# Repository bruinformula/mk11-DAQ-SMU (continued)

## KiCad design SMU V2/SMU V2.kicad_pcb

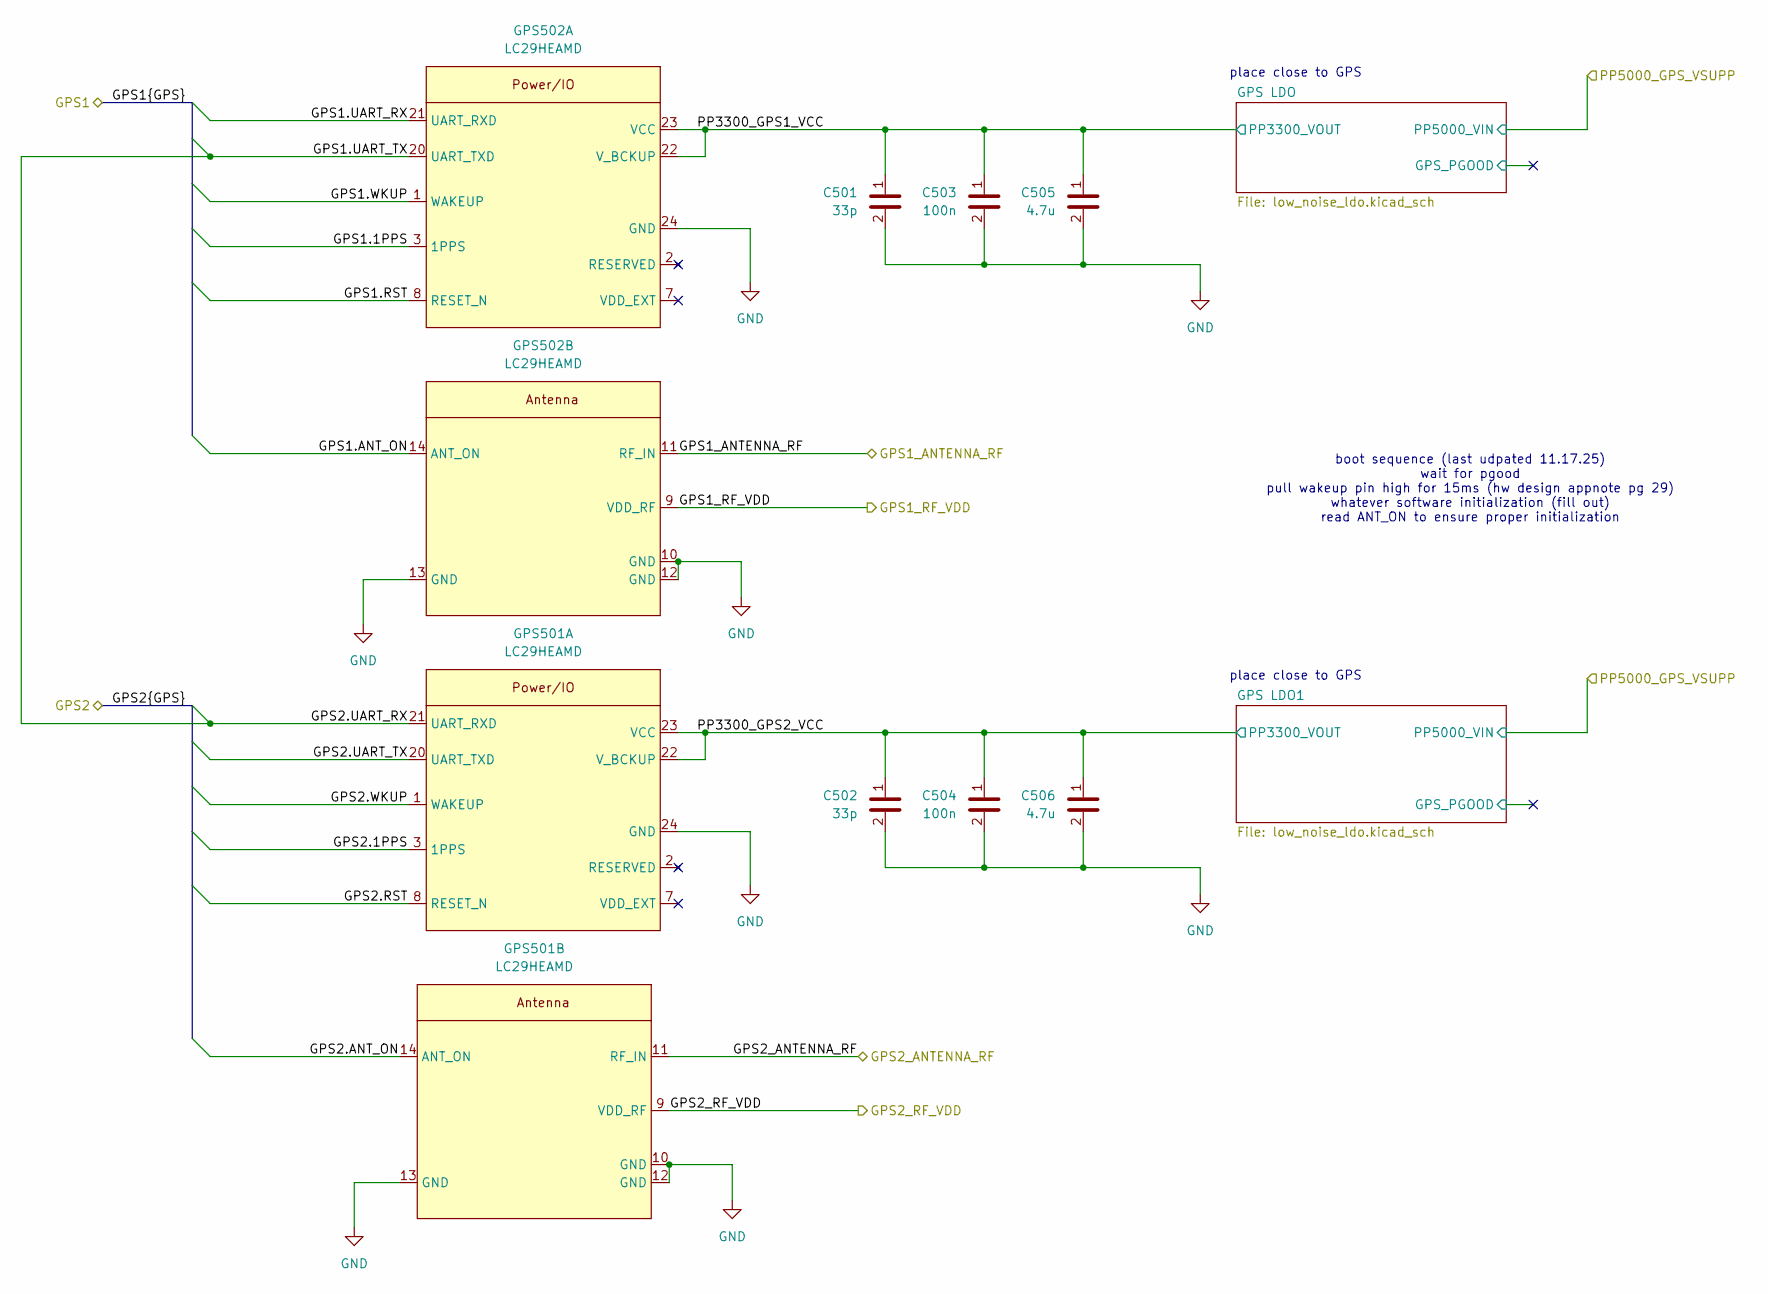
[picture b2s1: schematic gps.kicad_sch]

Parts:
C501, C502: 33p; C_0402_1005Metric_Pad0.74x0.62mm_HandSolder; LCSC P/N C1562
C503, C504: 100n; C_0402_1005Metric_Pad0.74x0.62mm_HandSolder; LCSC P/N C1525
C505, C506: 4.7u; C_0603_1608Metric_Pad1.08x0.95mm_HandSolder; LCSC P/N C19666
GPS501, GPS502: LC29HEAMD; Quectel LC49

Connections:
/Antenna1/GPS1_RF_VDD: GPS502.9 (VDD_RF); also elsewhere on the board
/Antenna2/GPS2_RF_VDD: GPS501.9 (VDD_RF); also elsewhere on the board
/GPS1.1PPS: GPS502.3 (1PPS); also elsewhere on the board
/GPS1.ANT_ON: GPS502.14 (ANT_ON); also elsewhere on the board
/GPS1.RST: GPS502.8 (RESET_N); also elsewhere on the board
/GPS1.UART_RX: GPS502.21 (UART_RXD); also elsewhere on the board
/GPS1.WKUP: GPS502.1 (WAKEUP); also elsewhere on the board
/GPS1_ANTENNA_RF: GPS502.11 (RF_IN); also elsewhere on the board
/GPS2.1PPS: GPS501.3 (1PPS); also elsewhere on the board
/GPS2.ANT_ON: GPS501.14 (ANT_ON); also elsewhere on the board
/GPS2.RST: GPS501.8 (RESET_N); also elsewhere on the board
/GPS2.UART_RX: GPS501.21 (UART_RXD), GPS502.20 (UART_TXD); also elsewhere on the board
/GPS2.UART_TX: GPS501.20 (UART_TXD); also elsewhere on the board
/GPS2.WKUP: GPS501.1 (WAKEUP); also elsewhere on the board
/GPS2_ANTENNA_RF: GPS501.11 (RF_IN); also elsewhere on the board
/GPS/PP3300_GPS1_VCC: C501.1, C503.1, C505.1, GPS502.22 (V_BCKUP), GPS502.23 (VCC); also elsewhere on the board
/GPS/PP3300_GPS2_VCC: C502.1, C504.1, C506.1, GPS501.22 (V_BCKUP), GPS501.23 (VCC); also elsewhere on the board
GND: C501.2, C502.2, C503.2, C504.2, C505.2, C506.2, GPS501.10 (GND), GPS501.12 (GND), GPS501.13 (GND), GPS501.24 (GND), GPS502.10 (GND), GPS502.12 (GND), GPS502.13 (GND), GPS502.24 (GND); also elsewhere on the board

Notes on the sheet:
boot sequence (last udpated 11.17.25) wait for pgood pull wakeup pin high for 15ms (hw design appnote pg 29) whatever software initialization (fill out) read ANT_ON to ensure proper initialization
place close to GPS

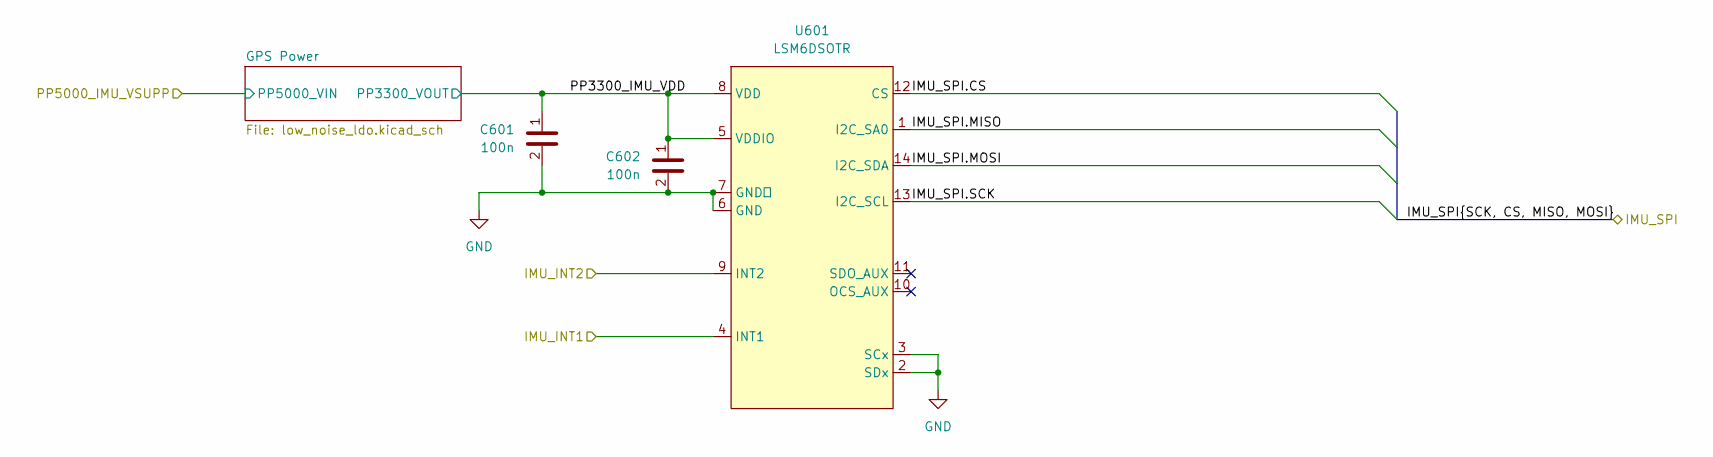
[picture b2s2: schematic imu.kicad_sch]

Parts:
C601, C602: 100n; C_0402_1005Metric_Pad0.74x0.62mm_HandSolder; LCSC P/N C1525
U601: LSM6DSOTR; LGA-14_3x2.5mm_P0.5mm_LayoutBorder3x4y; Manufacturer P/N LSM6DSOTR; Digikey P/N 497-18181-2-ND

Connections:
/IMU/IMU_INT1: U601.4 (INT1); also elsewhere on the board
/IMU/IMU_INT2: U601.9 (INT2); also elsewhere on the board
/IMU/PP3300_IMU_VDD: C601.1, C602.1, U601.5 (VDDIO), U601.8 (VDD); also elsewhere on the board
/IMU_SPI.CS: U601.12 (CS); also elsewhere on the board
/IMU_SPI.MISO: U601.1 (I2C_SA0); also elsewhere on the board
/IMU_SPI.MOSI: U601.14 (I2C_SDA); also elsewhere on the board
/IMU_SPI.SCK: U601.13 (I2C_SCL); also elsewhere on the board
GND: C601.2, C602.2, U601.2 (SDx), U601.3 (SCx), U601.6 (GND), U601.7 (GND); also elsewhere on the board

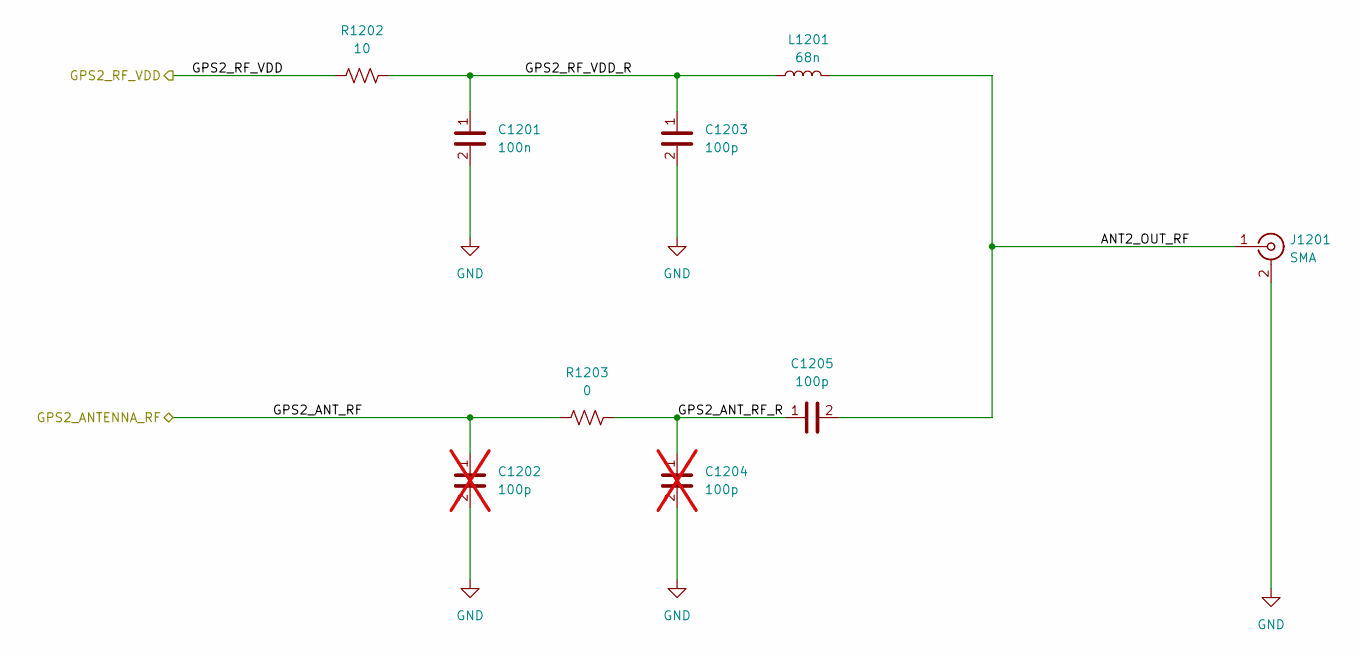
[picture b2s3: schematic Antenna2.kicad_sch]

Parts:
C1201: 100n; C_0402_1005Metric_Pad0.74x0.62mm_HandSolder; Manufacturer P/N CL05B104KB54PNC; LCSC P/N C307331
C1202, C1204: 100p; C_0402_1005Metric_Pad0.74x0.62mm_HandSolder; LCSC P/N C1546; not fitted
C1203, C1205: 100p; C_0402_1005Metric_Pad0.74x0.62mm_HandSolder; LCSC P/N C1546
J1201: SMA; THT SMA; Manufacturer P/N SMA-J-P-H-ST-TH1; Digikey P/N SAM8971-ND
L1201: 68n; L_0402_1005Metric_Pad0.77x0.64mm_HandSolder; Manufacturer P/N LQW15AN68NG0ZD; Digikey P/N 490-17700-2-ND
R1202: 10; R_0402_1005Metric_Pad0.72x0.64mm_HandSolder; Mouser P/N 708-RMCF0402FT10R0; Digikey P/N RMCF0402FT10R0CT-ND
R1203: 0; R_0402_1005Metric_Pad0.72x0.64mm_HandSolder; Mouser P/N 708-RMCF0402ZT0R00; Digikey P/N RMCF0402ZT0R00CT-ND

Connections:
/Antenna2/ANT2_OUT_RF: C1205.2, J1201.1, L1201.1
/Antenna2/GPS2_ANT_RF_R: C1204.1, C1205.1, R1203.2
/Antenna2/GPS2_RF_VDD: R1202.1; also elsewhere on the board
/Antenna2/GPS2_RF_VDD_R: C1201.1, C1203.1, L1201.2, R1202.2
/GPS2_ANTENNA_RF: C1202.1, R1203.1; also elsewhere on the board
GND: C1201.2, C1202.2, C1203.2, C1204.2, J1201.2; also elsewhere on the board

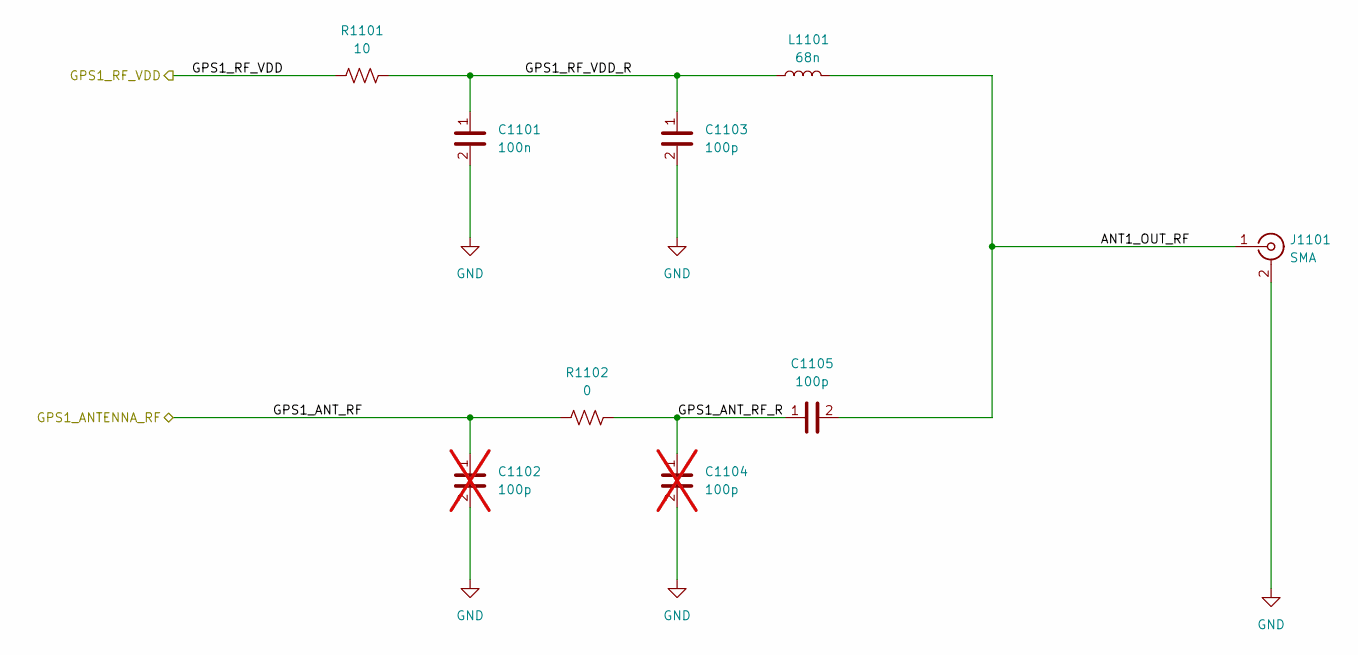
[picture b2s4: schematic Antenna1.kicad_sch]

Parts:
C1101: 100n; C_0402_1005Metric_Pad0.74x0.62mm_HandSolder; Manufacturer P/N CL05B104KB54PNC; LCSC P/N C307331
C1102, C1104: 100p; C_0402_1005Metric_Pad0.74x0.62mm_HandSolder; LCSC P/N C1546; not fitted
C1103, C1105: 100p; C_0402_1005Metric_Pad0.74x0.62mm_HandSolder; LCSC P/N C1546
J1101: SMA; THT SMA; Manufacturer P/N SMA-J-P-H-ST-TH1; Digikey P/N SAM8971-ND
L1101: 68n; L_0402_1005Metric_Pad0.77x0.64mm_HandSolder; Manufacturer P/N LQW15AN68NG0ZD; Digikey P/N 490-17700-2-ND
R1101: 10; R_0402_1005Metric_Pad0.72x0.64mm_HandSolder; Mouser P/N 708-RMCF0402FT10R0; Digikey P/N RMCF0402FT10R0CT-ND
R1102: 0; R_0402_1005Metric_Pad0.72x0.64mm_HandSolder; Mouser P/N 708-RMCF0402ZT0R00; Digikey P/N RMCF0402ZT0R00CT-ND

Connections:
/Antenna1/ANT1_OUT_RF: C1105.2, J1101.1, L1101.1
/Antenna1/GPS1_ANT_RF_R: C1104.1, C1105.1, R1102.2
/Antenna1/GPS1_RF_VDD: R1101.1; also elsewhere on the board
/Antenna1/GPS1_RF_VDD_R: C1101.1, C1103.1, L1101.2, R1101.2
/GPS1_ANTENNA_RF: C1102.1, R1102.1; also elsewhere on the board
GND: C1101.2, C1102.2, C1103.2, C1104.2, J1101.2; also elsewhere on the board

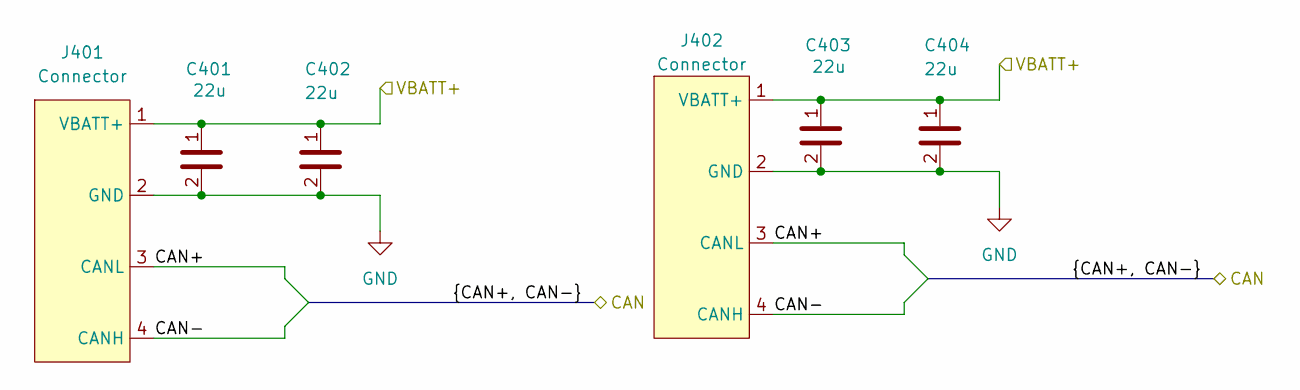
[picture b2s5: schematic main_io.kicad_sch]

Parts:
C401, C402, C403, C404: 22u; C_0805_2012Metric_Pad1.18x1.45mm_HandSolder; Mouser P/N 187-CL21A226MAYNNNE
J401, J402: Connector; Molex_Micro-Fit_3.0_43650-0400_1x04_P3.00mm_Horizontal; Manufacturer P/N 0436500401; Digikey P/N WM1867-ND

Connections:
/CAN+: J401.3 (CANL), J402.3 (CANL); also elsewhere on the board
/CAN-: J401.4 (CANH), J402.4 (CANH); also elsewhere on the board
/Main IO/VBATT+: C401.1, C402.1, C403.1, C404.1, J401.1 (VBATT+), J402.1 (VBATT+); also elsewhere on the board
GND: C401.2, C402.2, C403.2, C404.2, J401.2 (GND), J402.2 (GND); also elsewhere on the board

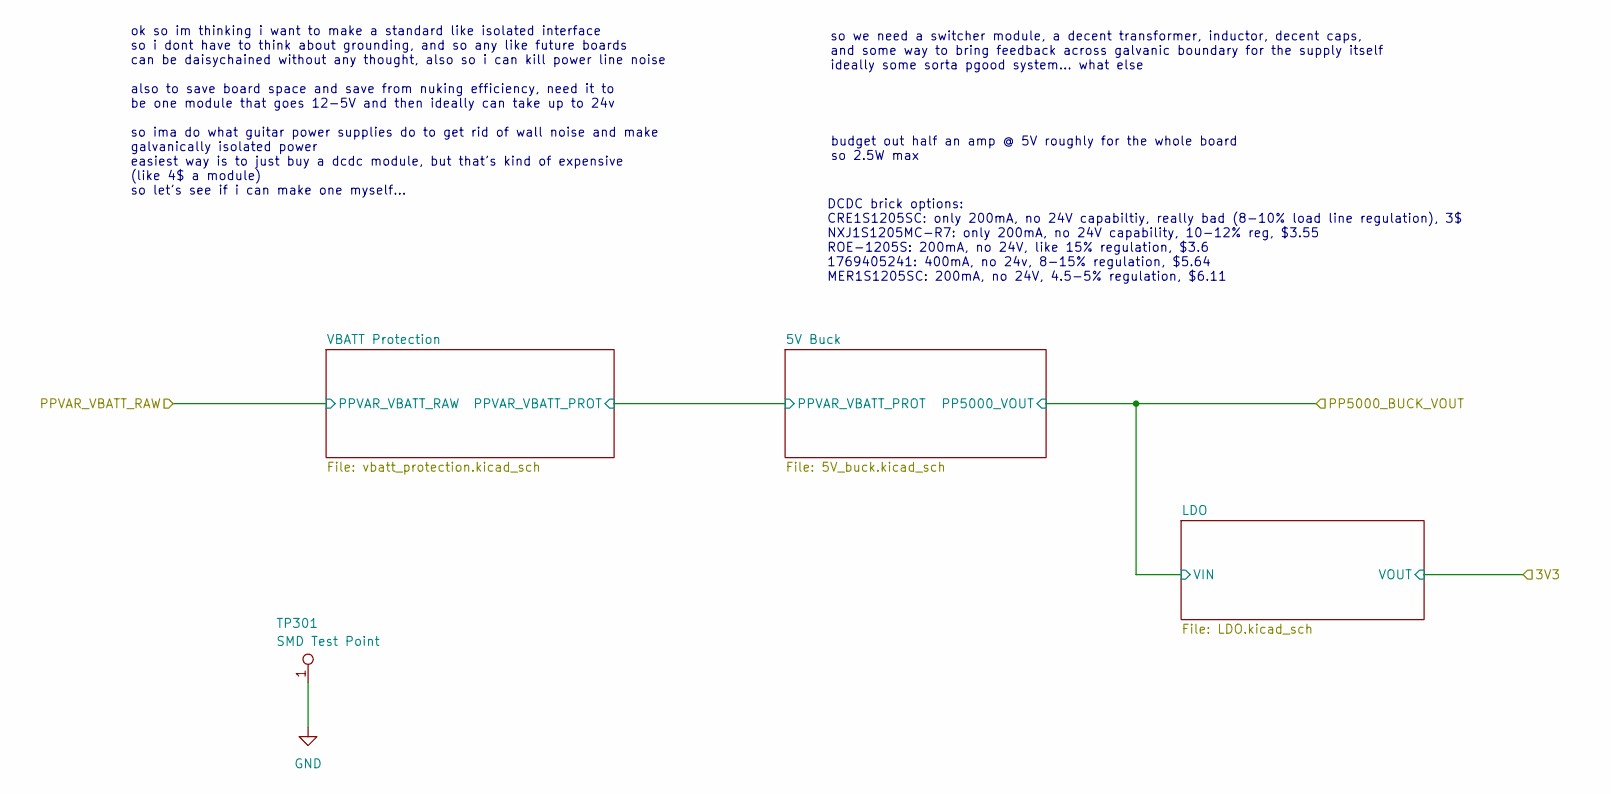
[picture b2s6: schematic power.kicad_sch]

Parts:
TP301: SMD Test Point; TestPoint_Keystone_5019_Miniature; Manufacturer P/N RH-5019; Digikey P/N 36-5019CT-ND

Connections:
GND: TP301.1; also elsewhere on the board

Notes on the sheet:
ok so im thinking i want to make a standard like isolated interface so i dont have to think about grounding, and so any like future boards can be daisychained without any thought, also so i can kill power line noise also to save board space and save from nuking efficiency, need it to be one module 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
so we need a switcher module, a decent transformer, inductor, decent caps, and some way to bring feedback across galvanic boundary for the supply itself ideally some sorta pgood system... what else
DCDC brick options: CRE1S1205SC: only 200mA, no 24V capabiltiy, really bad (8-10% load line regulation), 3$ NXJ1S1205MC-R7: only 200mA, no 24V capability, 10-12% reg, $3.55 ROE-1205S: 200mA, no 24V, like 15% regulation, $3.6 1769405241: 400mA, no 24v, 8-15% regulation, $5.64 MER1S1205SC: 200mA, no 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
budget out half an amp @ 5V roughly for the whole board so 2.5W max

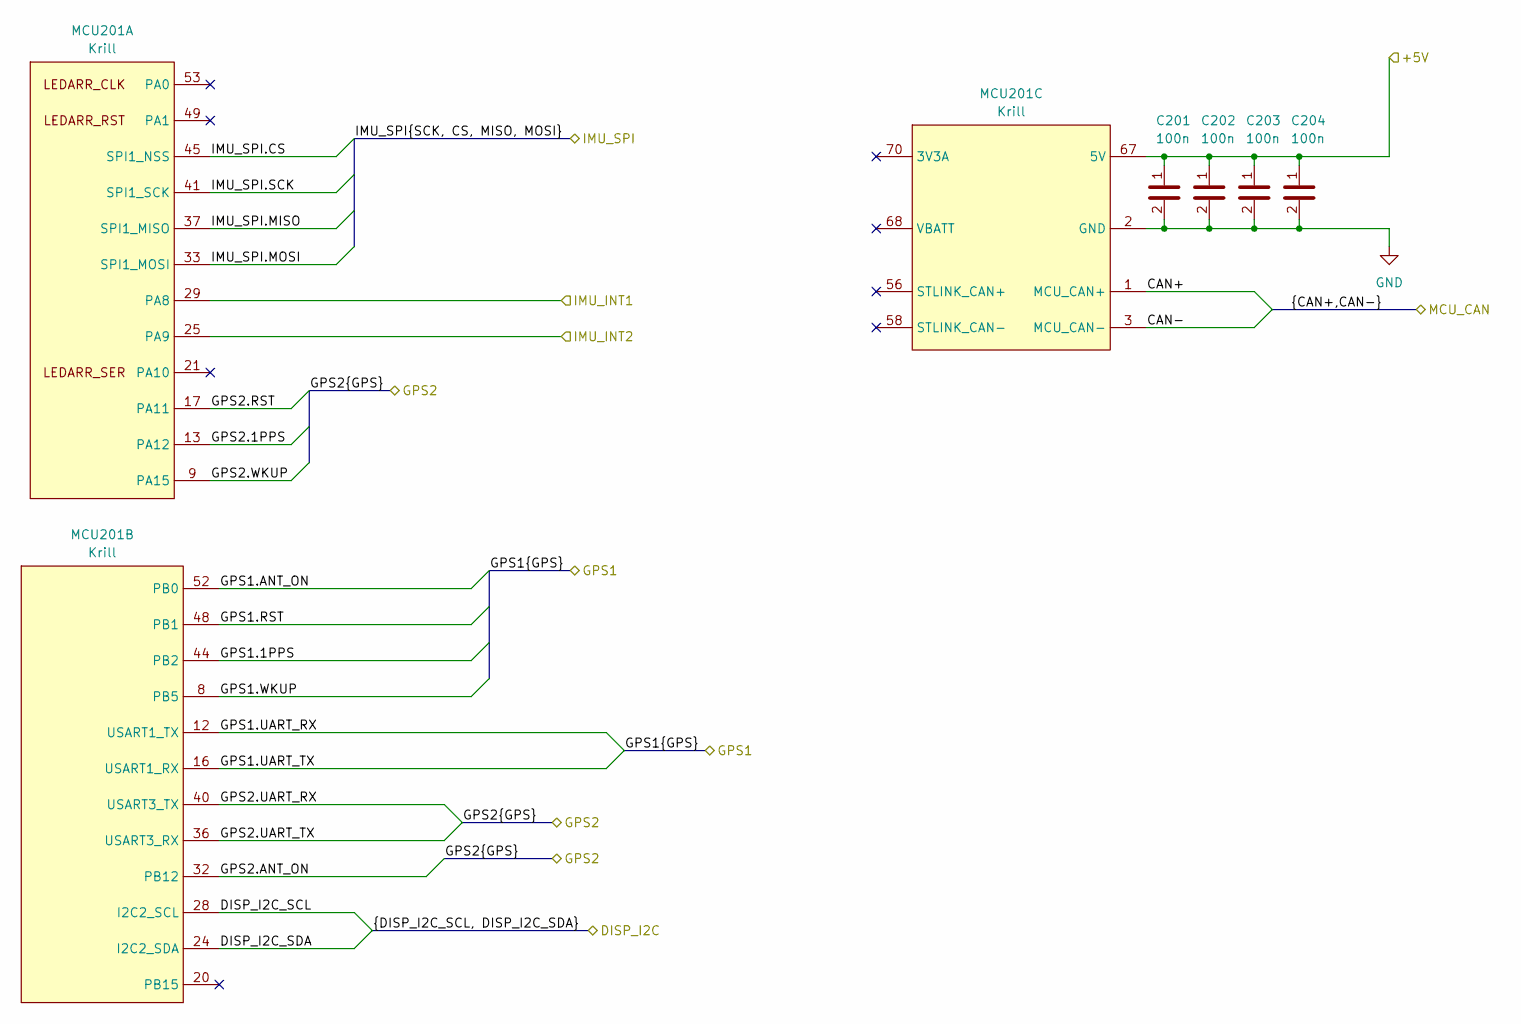
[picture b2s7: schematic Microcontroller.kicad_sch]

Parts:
C201, C202, C203, C204: 100n; C_0402_1005Metric_Pad0.74x0.62mm_HandSolder; LCSC P/N C1525
MCU201: Krill; Manufacturer P/N 2E0BC21-S85BM-7H; Digikey P/N 609-MDT850M01501CT-ND

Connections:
+5V: C201.1, C202.1, C203.1, C204.1, MCU201.67 (5V), MCU201.69 (5V), MCU201.71 (5V); also elsewhere on the board
/CAN+: MCU201.1 (MCU_CAN+); also elsewhere on the board
/CAN-: MCU201.3 (MCU_CAN-); also elsewhere on the board
/GPS1.1PPS: MCU201.44 (PB2); also elsewhere on the board
/GPS1.ANT_ON: MCU201.52 (PB0); also elsewhere on the board
/GPS1.RST: MCU201.48 (PB1); also elsewhere on the board
/GPS1.UART_RX: MCU201.12 (USART1_TX); also elsewhere on the board
/GPS1.WKUP: MCU201.8 (PB5); also elsewhere on the board
/GPS2.1PPS: MCU201.13 (PA12); also elsewhere on the board
/GPS2.ANT_ON: MCU201.32 (PB12); also elsewhere on the board
/GPS2.RST: MCU201.17 (PA11); also elsewhere on the board
/GPS2.UART_RX: MCU201.16 (USART1_RX), MCU201.40 (USART3_TX); also elsewhere on the board
/GPS2.UART_TX: MCU201.36 (USART3_RX); also elsewhere on the board
/GPS2.WKUP: MCU201.9 (PA15); also elsewhere on the board
/IMU/IMU_INT1: MCU201.29 (PA8); also elsewhere on the board
/IMU/IMU_INT2: MCU201.25 (PA9); also elsewhere on the board
/IMU_SPI.CS: MCU201.45 (SPI1_NSS); also elsewhere on the board
/IMU_SPI.MISO: MCU201.37 (SPI1_MISO); also elsewhere on the board
/IMU_SPI.MOSI: MCU201.33 (SPI1_MOSI); also elsewhere on the board
/IMU_SPI.SCK: MCU201.41 (SPI1_SCK); also elsewhere on the board
/Microcontroller/DISP_I2C_SCL: MCU201.28 (I2C2_SCL)
/Microcontroller/DISP_I2C_SDA: MCU201.24 (I2C2_SDA)
GND: C201.2, C202.2, C203.2, C204.2, MCU201.2 (GND), MCU201.4 (GND), MCU201.5 (GND), MCU201.6 (GND), MCU201.7 (GND), MCU201.10 (GND), MCU201.11 (GND), MCU201.14 (GND), MCU201.15 (GND), MCU201.18 (GND), MCU201.19 (GND), MCU201.22 (GND), MCU201.23 (GND), MCU201.26 (GND), MCU201.27 (GND), MCU201.30 (GND), MCU201.31 (GND), MCU201.34 (GND), MCU201.35 (GND), MCU201.38 (GND), MCU201.39 (GND), MCU201.42 (GND), MCU201.43 (GND), MCU201.46 (GND), MCU201.47 (GND), MCU201.50 (GND), MCU201.51 (GND), MCU201.54 (GND), MCU201.55 (GND), MCU201.57 (GND), MCU201.73 (GND), MCU201.75 (GND); also elsewhere on the board

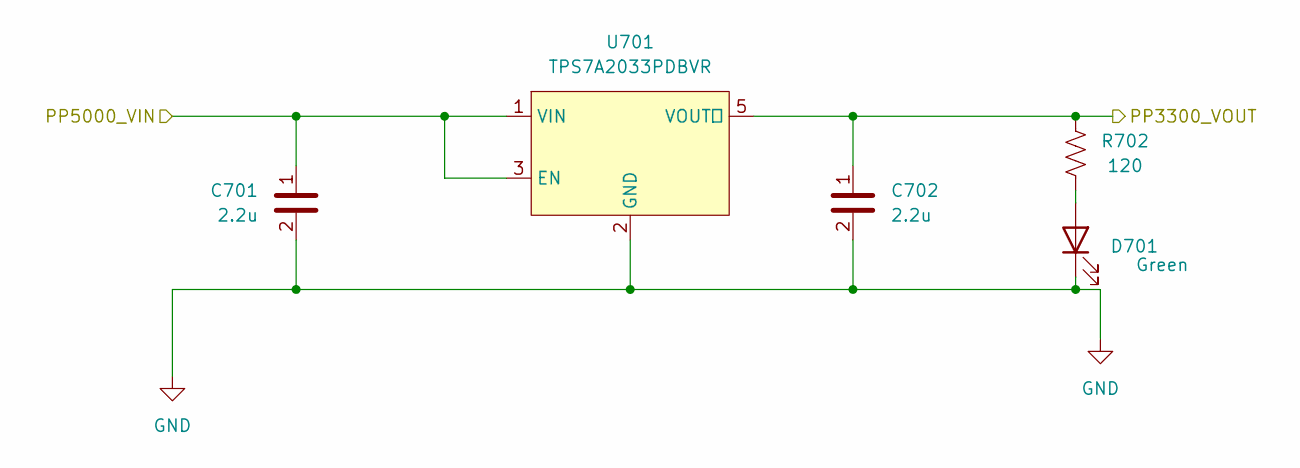
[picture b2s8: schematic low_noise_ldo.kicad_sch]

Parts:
C701, C702: 2.2u; C_0402_1005Metric_Pad0.74x0.62mm_HandSolder; LCSC P/N C12530
D701: Green; D_0805_2012Metric_Pad1.15x1.40mm_HandSolder; Mouser P/N 755-SMLMN2ECTT86C; Digikey P/N 846-SMLMN2ECTT86CCT-ND
R702: 120; R_0603_1608Metric_Pad0.98x0.95mm_HandSolder; Mouser P/N 708-RMCF0603FT120R; Digikey P/N RMCF0603FT120RCT-ND
U701: TPS7A2033PDBVR; SOT-23-5_HandSoldering; Manufacturer P/N TPS7A2033PDBVR; Digikey P/N 296-TPS7A2033PDBVRCT-ND

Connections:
+5V: C701.1, U701.1 (VIN), U701.3 (EN); also elsewhere on the board
/GPS/PP3300_GPS1_VCC: C702.1, R702.1, U701.5 (VOUT); also elsewhere on the board
GND: C701.2, C702.2, D701.1 (K), U701.2 (GND); also elsewhere on the board
unnamed: D701.2 (A), R702.2

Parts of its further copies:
C801, C802, C901, C902: 2.2u; C_0402_1005Metric_Pad0.74x0.62mm_HandSolder; LCSC P/N C12530
D801, D901: Green; D_0805_2012Metric_Pad1.15x1.40mm_HandSolder; Mouser P/N 755-SMLMN2ECTT86C; Digikey P/N 846-SMLMN2ECTT86CCT-ND
R802, R902: 120; R_0603_1608Metric_Pad0.98x0.95mm_HandSolder; Mouser P/N 708-RMCF0603FT120R; Digikey P/N RMCF0603FT120RCT-ND
U801, U901: TPS7A2033PDBVR; SOT-23-5_HandSoldering; Manufacturer P/N TPS7A2033PDBVR; Digikey P/N 296-TPS7A2033PDBVRCT-ND

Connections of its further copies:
+5V: C801.1, C901.1, U801.1 (VIN), U801.3 (EN), U901.1 (VIN), U901.3 (EN); also elsewhere on the board
/GPS/PP3300_GPS2_VCC: C802.1, R802.1, U801.5 (VOUT); also elsewhere on the board
/IMU/PP3300_IMU_VDD: C902.1, R902.1, U901.5 (VOUT); also elsewhere on the board
GND: C801.2, C802.2, C901.2, C902.2, D801.1 (K), D901.1 (K), U801.2 (GND), U901.2 (GND); also elsewhere on the board
unnamed: D801.2 (A), R802.2
unnamed: D901.2 (A), R902.2

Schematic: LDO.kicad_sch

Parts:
C1401, C1402, C1403, C1404: 10u; C_0603_1608Metric_Pad1.08x0.95mm_HandSolder; Mouser P/N 81-GRM188R61E106MA3D
D1401: Green; D_0805_2012Metric_Pad1.15x1.40mm_HandSolder; Mouser P/N 755-SMLMN2ECTT86C; Digikey P/N 846-SMLMN2ECTT86CCT-ND
R1401: 220; R_0402_1005Metric_Pad0.72x0.64mm_HandSolder; Mouser P/N 708-RMCF0402FT220R; Digikey P/N RMCF0402FT220RCT-ND
U1401: AMS1117-3.3; SOT-223-3_TabPin2; Mouser P/N 637-LDI1117-3.3H; Digikey P/N 5272-AMS1117-3.3CT-ND

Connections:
+3V3: C1403.1, C1404.1, R1401.2, U1401.2 (VO)
+5V: C1401.1, C1402.1, U1401.3 (VI); also elsewhere on the board
GND: C1401.2, C1402.2, C1403.2, C1404.2, D1401.1 (K), U1401.1 (GND); also elsewhere on the board
unnamed: D1401.2 (A), R1401.1

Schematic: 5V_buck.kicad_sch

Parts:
C1001, C1002: 22u; C_0603_1608Metric_Pad1.08x0.95mm_HandSolder; LCSC P/N C59461
C1003: 1.8p; C_0805_2012Metric_Pad1.18x1.45mm_HandSolder; Mouser P/N 581-600F1R8BT; Digikey P/N 1284-1034-1-ND
C1004: 10n; C_0603_1608Metric_Pad1.08x0.95mm_HandSolder; Mouser P/N 77-VJ0603Y103KXAAC; Digikey P/N 720-1376-1-ND
C1005, C1006, C1007, C1008, C1009: 100u; C_1206_3216Metric_Pad1.33x1.80mm_HandSolder; LCSC P/N C15008
D1001: 550m; D_SMA_Handsoldering; Mouser P/N 750-SS54-HF; LCSC P/N C22452
R1001: 180k; R_0805_2012Metric_Pad1.20x1.40mm_HandSolder; Mouser P/N 708-RMCF0805FT180K; Digikey P/N RMCF0805FT180KCT-ND
R1002: 10k; R_0402_1005Metric_Pad0.72x0.64mm_HandSolder; Mouser P/N 708-RMCF0402FT10K0; Digikey P/N RMCF0402FT10K0CT-ND
R1003: 3.3k; R_0402_1005Metric_Pad0.72x0.64mm_HandSolder; Mouser P/N 708-RMCF0402FT3K30; Digikey P/N RMCF0402FT3K30CT-ND
U1001: TPS5430DDAR; TI_SO-PowerPAD-8; Mouser P/N 595-TPS5430DDAR; Digikey P/N 296-26988-1-ND
U1002: ETQ-P3M150KVN; BWVS005050404R7M00; Manufacturer P/N ETQ-P3M150KVN; Digikey P/N P19763CT-ND

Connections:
+5V: C1005.1, C1006.1, C1007.1, C1008.1, C1009.1, R1002.2, U1002.2; also elsewhere on the board
/Power/5V Buck/BUCK_VSENSE: R1002.1, R1003.2, U1001.4 (VSENSE)
/Power/5V Buck/PPVAR_VBATT_PROT: C1001.1, C1002.1, C1003.1, U1001.7 (VIN); also elsewhere on the board
/Power/5V Buck/Rsnub: C1003.2, R1001.1
/Power/5V Buck/SWITCH_NODE: C1004.2, D1001.1 (K), R1001.2, U1001.8 (PH), U1002.1
GND: C1001.2, C1002.2, C1005.2, C1006.2, C1007.2, C1008.2, C1009.2, D1001.2 (A), R1003.1, U1001.6 (GND), U1001.9 (GNDPAD); also elsewhere on the board
unnamed: C1004.1, U1001.1 (BOOT)

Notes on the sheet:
RC Snubber design: goal is to get Q=1 (critically damped) for the LC tank between U1002 and U1001 internal FET so, we take R=2*pi*F_sw*L (from a rlc shit i forgot) sim says switching freq is 2GHz R=2*3.14*2*10^9*15*10^-6 = 188495 chat what does this mean! now size C based off power..; P = C * Vcc^2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

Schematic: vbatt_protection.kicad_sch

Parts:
D1201: Green; D_0805_2012Metric_Pad1.15x1.40mm_HandSolder; Mouser P/N 755-SMLMN2ECTT86C; Digikey P/N 846-SMLMN2ECTT86CCT-ND
F1201: 500mA; Fuse_1812_4532Metric; Manufacturer P/N 0ZCG0050AF2C; Digikey P/N 5923-0ZCG0050AF2CCT-ND
Q1201: SI2301CDS-T1-GE3; SOT-23-3; Mouser P/N 781-SI2301CDS-T1-GE3; LCSC P/N C10487
R1201: 1.8k; R_0603_1608Metric_Pad0.98x0.95mm_HandSolder; Mouser P/N 708-RMCF0603FT1K80; Digikey P/N RMCF0603FT1K80CT-ND
TVS1201: 16Vrwm; D_SMA-SMB_Universal_Handsoldering; Manufacturer P/N SMBJ16A; Digikey P/N SMBJ16ABCT-ND

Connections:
/Main IO/VBATT+: Q1201.2 (S); also elsewhere on the board
/Power/5V Buck/PPVAR_VBATT_PROT: F1201.2, R1201.1; also elsewhere on the board
GND: D1201.1 (K), Q1201.1 (G), TVS1201.2; also elsewhere on the board
unnamed: D1201.2 (A), R1201.2
unnamed: F1201.1, Q1201.3 (D), TVS1201.1

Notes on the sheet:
board-wide PGOOD LED

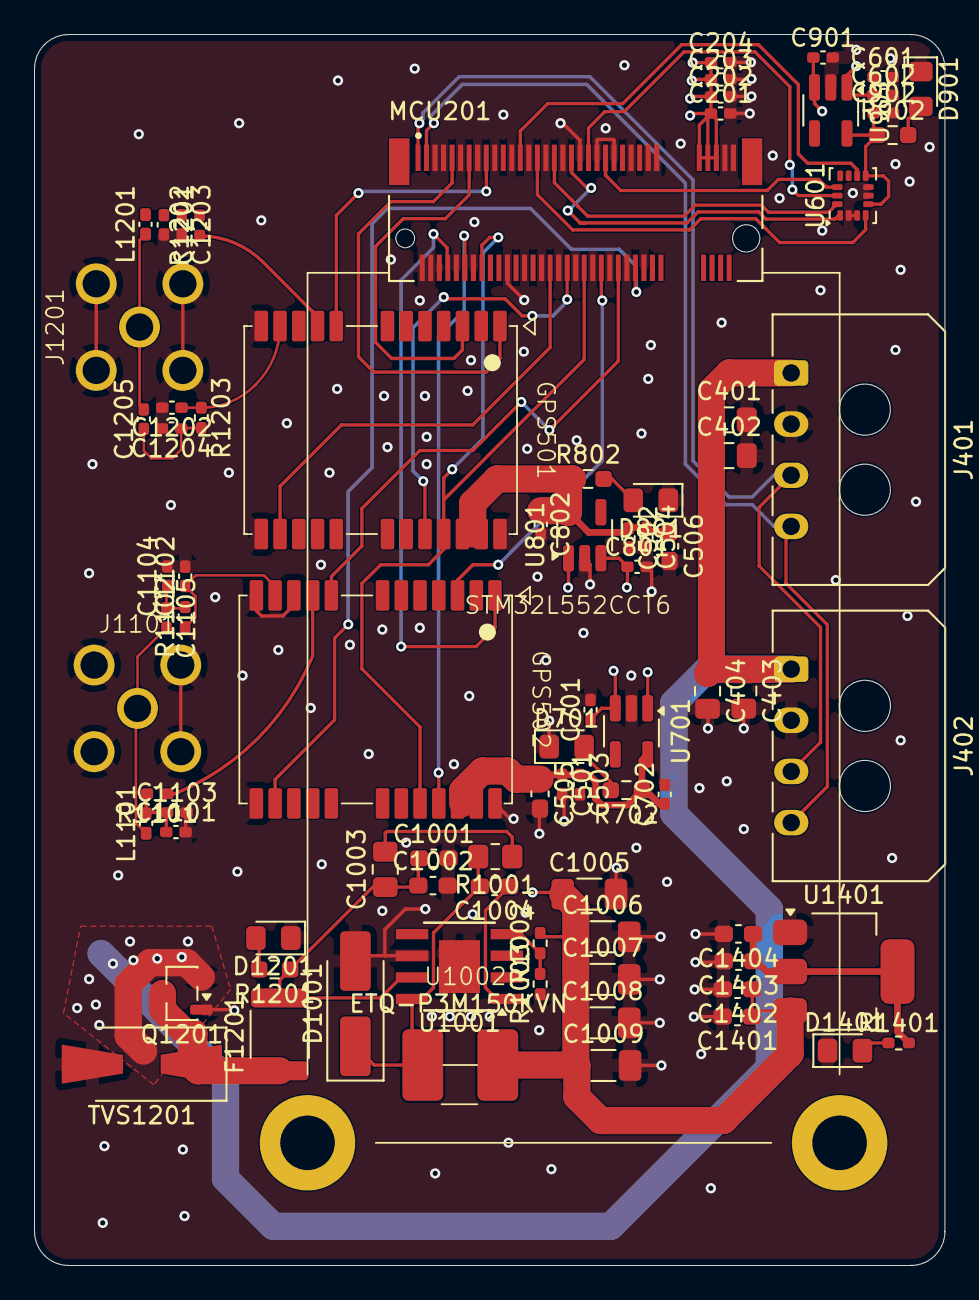
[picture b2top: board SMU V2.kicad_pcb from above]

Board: 4 copper layers, 53.4 x 72.2 mm, 83 parts (1 on the bottom side), 47 nets.

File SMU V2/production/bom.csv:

Designator,Footprint,Quantity,Value,LCSC Part #
"C1001, C1002",0603,2,22u,C59461
C1003,0805,1,1.8p,C376870
C1004,0603,1,10n,C57112
"C1005, C1006, C1007, C1008, C1009",1206,5,100u,C15008
"C1101, C1201",0402,2,100n,C307331
"C1102, C1103, C1104, C1105, C1202, C1203, C1204, C1205",0402,8,100p,C1546
"C1401, C1402, C1403, C1404",0603,4,10u,C96446
"C201, C202, C203, C204, C503, C504, C601, C602",0402,8,100n,C1525
"C401, C402, C403, C404",0805,4,22u,C45783
"C501, C502",0402,2,33p,C1562
"C505, C506",0603,2,4.7u,C19666
"C701, C702, C801, C802, C901, C902",0402,6,2.2u,C12530
D1001,D_SMA_Handsoldering,1,550m,C22452
"D1201, D1401, D701, D801, D901",0805,5,Green,C2297
F1201,1812,1,500mA,C3762102
"GPS501, GPS502",Quectel LC49,2,LC29HEAMD,
"J1101, J1201",THT SMA,2,SMA,C5199904
"J401, J402",Molex_Micro-Fit_3.0_43650-0400_1x04_P3.00mm_Horizontal,2,Connector,
"L1101, L1201",0402,2,68n,C2044127
MCU201,Krill,1,Krill,C410529
Q1201,SOT-23-3,1,SI2301CDS-T1-GE3,C10487
R1001,0805,1,180k,C17501
R1002,0402,1,10k,C25744
R1003,0402,1,3.3k,C25890
"R1101, R1202",0402,2,10,C25077
"R1102, R1203",0402,2,0,C17168
R1201,0603,1,1.8k,C4177
R1401,0402,1,220,C25091
"R702, R802, R902",0603,3,120,C22787
TP301,TestPoint_Keystone_5019_Miniature,1,SMD Test Point,C5199800
TVS1201,D_SMA-SMB_Universal_Handsoldering,1,16Vrwm,C19077571
U1001,TI_SO-PowerPAD-8,1,TPS5430DDAR,C9864
U1002,BWVS005050404R7M00,1,ETQ-P3M150KVN,C3223274
U1401,SOT-223-3_TabPin2,1,AMS1117-3.3,C6186
U601,LGA-14_3x2.5mm_P0.5mm_LayoutBorder3x4y,1,LSM6DSOTR,C481766
"U701, U801, U901",SOT-23-5_HandSoldering,3,TPS7A2033PDBVR,TPS7A2033PDBVR
